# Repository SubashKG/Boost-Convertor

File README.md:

View this project on [CADLAB.io](https://cadlab.io/project/29072). 

# Boost-Convertor

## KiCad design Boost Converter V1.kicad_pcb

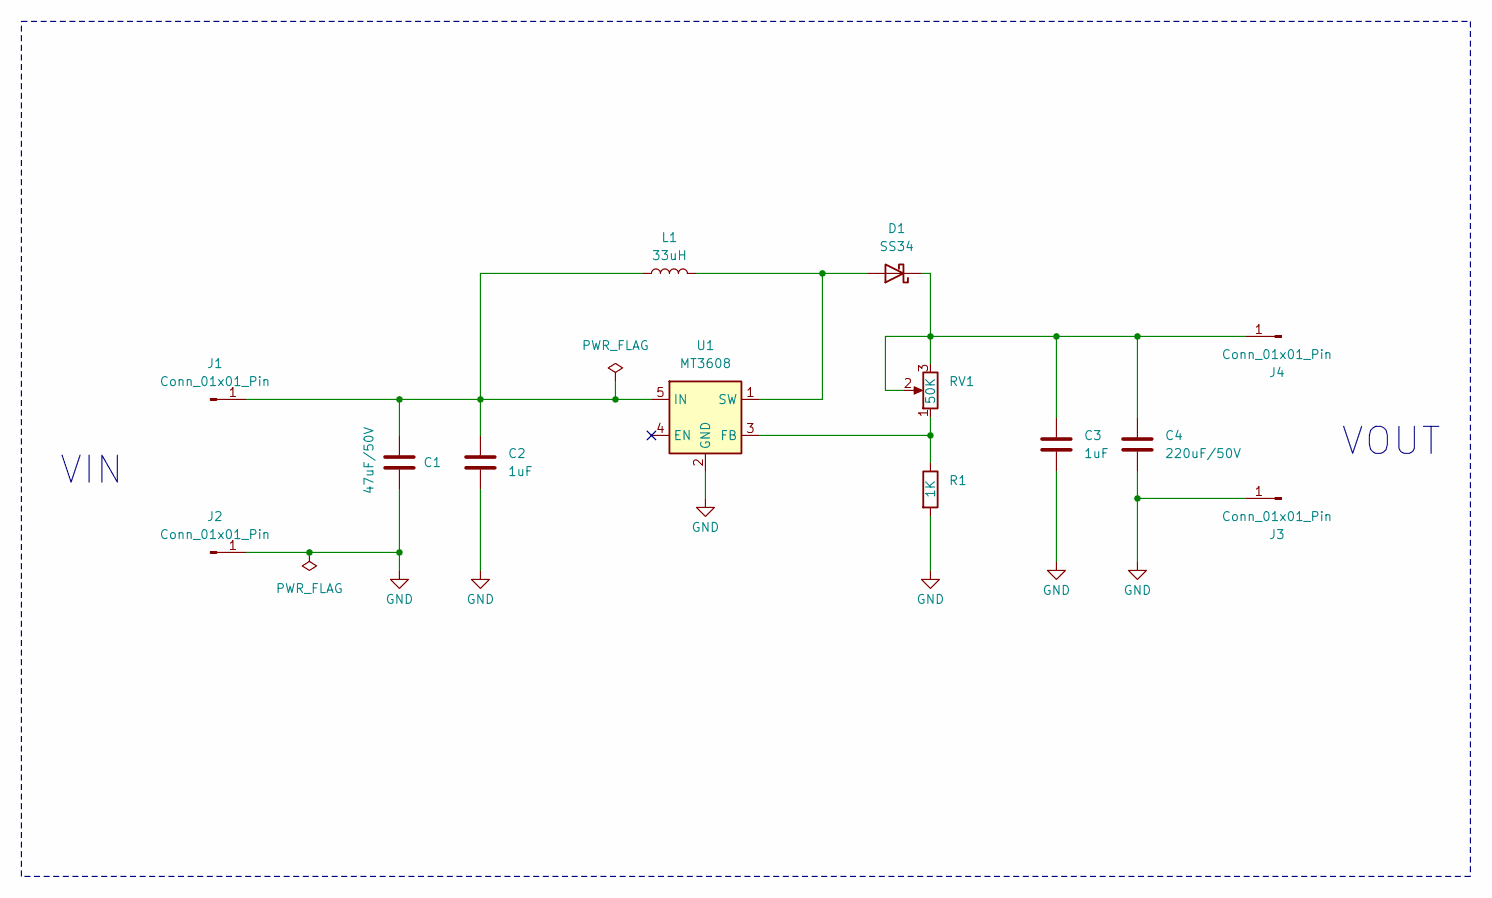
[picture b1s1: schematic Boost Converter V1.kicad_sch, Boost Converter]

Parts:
C1: 47uF/50V; C_Radial_D6.3mm_H11.0mm_P2.50mm
C2, C3: 1uF; C_0805_2012Metric
C4: 220uF/50V; C_Radial_D6.3mm_H11.0mm_P2.50mm
D1: SS34; D_SMA
J1, J2, J3, J4: Conn_01x01_Pin; PinHeader_1x01_P2.54mm_Vertical
L1: 33uH; L_12x12mm_H8mm
R1: 1K; R_1206_3216Metric
RV1: 50K; Potentiometer_Bourns_3296W_Vertical
U1: MT3608; SOT-23-6

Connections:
GND: C1.2, C2.2, C3.2, C4.2, J2.1, J3.1, R1.2, U1.2 (GND)
unnamed: D1.2 (A), L1.2, U1.1 (SW)
unnamed: C3.1, C4.1, D1.1 (K), J4.1, RV1.2, RV1.3
unnamed: C1.1, C2.1, J1.1, L1.1, U1.5 (IN)
unnamed: R1.1, RV1.1, U1.3 (FB)

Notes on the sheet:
VIN
VOUT

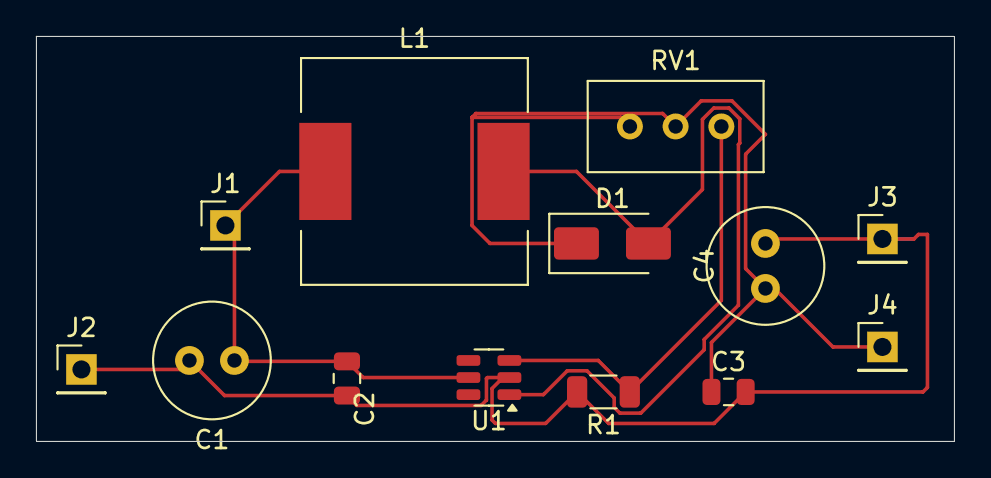
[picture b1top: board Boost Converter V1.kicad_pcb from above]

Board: 2 copper layers, 51.0 x 22.5 mm, 13 parts (0 on the bottom side), 5 nets.

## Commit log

2025-03-30 Backlink to CADLAB.io has been added.
2025-03-30 Boost convertor
